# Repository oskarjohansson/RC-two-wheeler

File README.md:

# RC two wheeler
A 4 kW RC car with overkill BLDC motors and two VESCs and a 5 kW LiPo.  

## Hardware
- Flipsky VESC v4.12 x 2
- KEDA 63-64 190KV 2kW x 2
- Arduino Nano x2
- nRF24 x2
- 3S 60C 4000 mAh Turnigy Heavy duty LiPo
- Joystick 
- ~~2P2S N.E.S.E module x 2~~
- ~~Samsung 25E á 20A x 8~~
- ~~FrSky transmitter~~
- ~~RF Reciever~~

### PCB
- PWM/5V/GND in
- Nano
- nRF24 
- ON/OFF
- Battery
- Joystick  

## Software
- VESC Tool v0.95. 
- VSCode project for Nano.

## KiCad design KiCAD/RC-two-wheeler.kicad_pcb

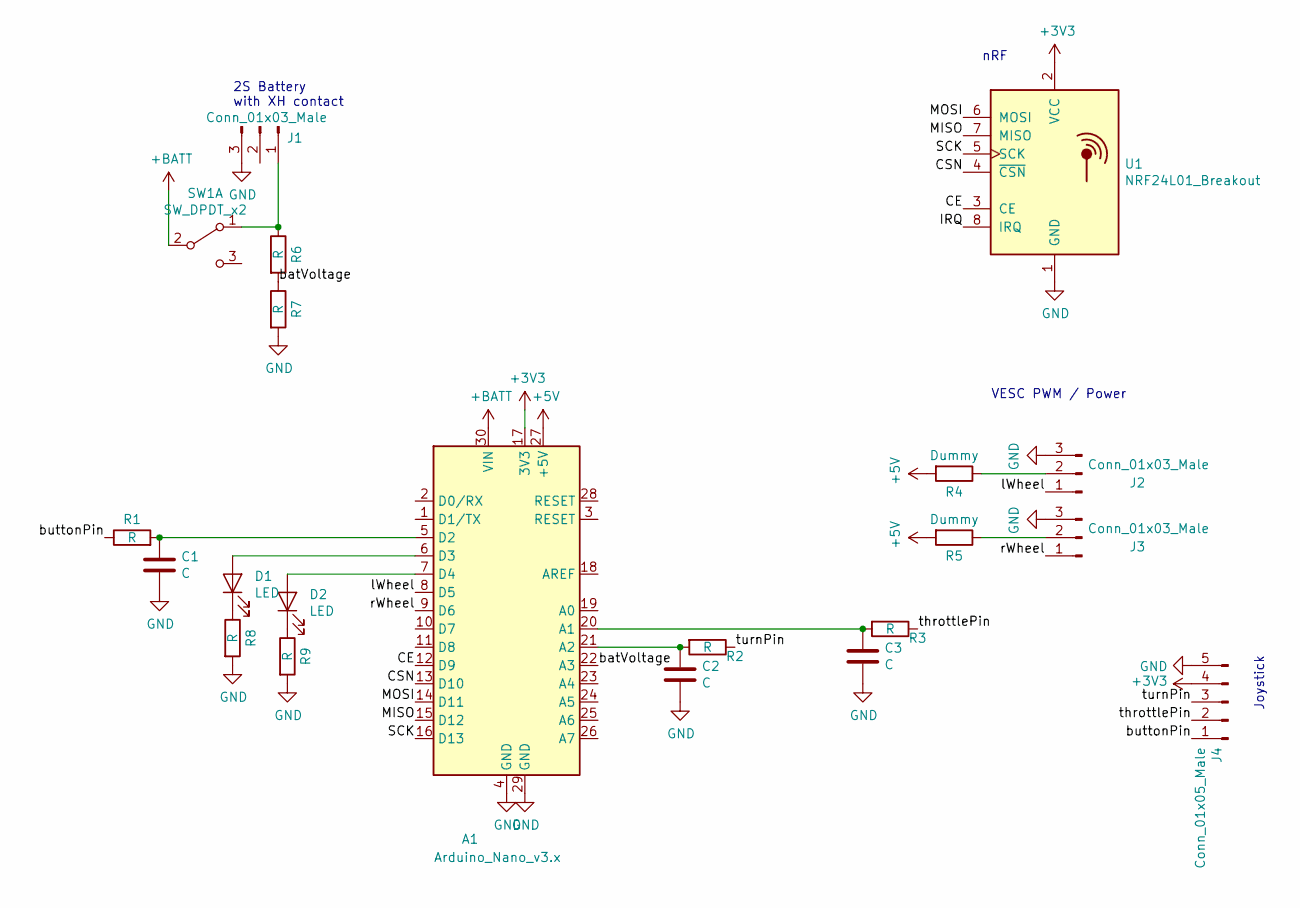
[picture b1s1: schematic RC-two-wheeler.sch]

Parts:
A1: Arduino_Nano_v3.x; Arduino_Nano
C1, C2, C3: C; C_0603_1608Metric_Pad1.05x0.95mm_HandSolder
D1, D2: LED; LED_0603_1608Metric_Pad1.05x0.95mm_HandSolder
J1, J2, J3: Conn_01x03_Male; JST_XH_B3B-XH-A_1x03_P2.50mm_Vertical
J4: Conn_01x05_Male; JST_XH_B5B-XH-A_1x05_P2.50mm_Vertical
R1, R2, R3, R6, R7, R8, R9: R; R_0603_1608Metric_Pad1.05x0.95mm_HandSolder
R4, R5: Dummy; R_0603_1608Metric_Pad1.05x0.95mm_HandSolder
SW1: SW_DPDT_x2; JS202011SCQN
U1: NRF24L01_Breakout; nRF24L01_Breakout

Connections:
+3V3: A1.17 (3V3), J4.4, U1.2 (VCC)
+5V: A1.27 (+5V), R4.2, R5.2
+BATT: A1.30 (VIN), SW1.2 (B)
/CE: A1.12 (D9), U1.3 (CE)
/CSN: A1.13 (D10), U1.4 (~CSN)
/IRQ: U1.8 (IRQ)
/MISO: A1.15 (D12), U1.7 (MISO)
/MOSI: A1.14 (D11), U1.6 (MOSI)
/SCK: A1.16 (D13), U1.5 (SCK)
/batVoltage: A1.22 (A3), R6.2, R7.1
/buttonPin: J4.1, R1.1
/lWheel: A1.8 (D5), J2.1
/rWheel: A1.9 (D6), J3.1
/throttlePin: J4.2, R3.1
/turnPin: J4.3, R2.1
GND: A1.4 (GND), A1.29 (GND), C1.2, C2.2, C3.2, J1.3, J2.3, J3.3, J4.5, R7.2, R8.2, R9.2, U1.1 (GND)
unnamed: A1.5 (D2), C1.1, R1.2
unnamed: A1.6 (D3), D1.2 (A)
unnamed: A1.7 (D4), D2.2 (A)
unnamed: A1.20 (A1), C3.1, R3.2
unnamed: A1.21 (A2), C2.1, R2.2
unnamed: D1.1 (K), R8.1
unnamed: D2.1 (K), R9.1
unnamed: J1.1, R6.1, SW1.1 (A)
unnamed: J2.2, R4.1
unnamed: J3.2, R5.1

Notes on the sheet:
VESC PWM / Power
Joystick
2S Battery with XH contact
nRF

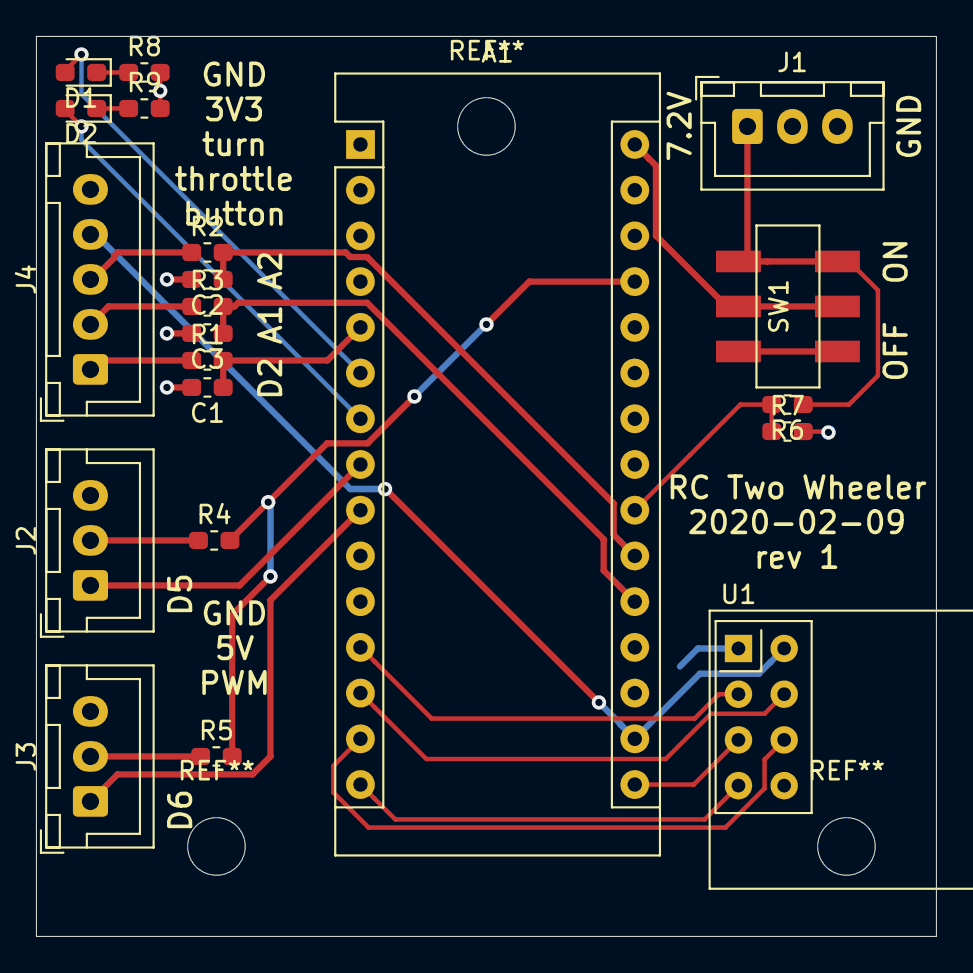
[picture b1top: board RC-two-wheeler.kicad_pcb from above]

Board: 2 copper layers, 50.0 x 50.0 mm, 21 parts (0 on the bottom side), 25 nets.

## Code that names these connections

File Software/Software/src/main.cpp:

/**
 * @file main.cpp
 * @author Oskar Johansson (oskar@irisnet.se)
 * @brief This project is to work with 2 MCU and 2 nRF24 to communicate throttle and turn. Based on 
 *        https://github.com/caselabbet/case-rc-car by Isak Åslund. 
 * @version 0.1
 * @date 2020-01-29 
 */
#include <Arduino.h>
#include <SoftwareSerial.h>
#include <Servo.h>
#include <RF24.h>


// Choose which to compile for 
#define reciever
//#define transmitter 
#define DEBUG

/**
 * To reuse same code for reciever and trasmitter 
 */


/**
 * Pin definition, same for reciever as transmitter
 */
#define lWheelPin 5
#define rWheelPin 6
#define throttlePin A1
#define turnPin A2
#define CE 9 
#define CSN 10

RF24 radio(CE,CSN); 
const byte address[6] = "00010";    // Adress for communicating
unsigned long lastData = 0;         // Used for knowing if data has been received recently
unsigned long lasttime = millis();  // To track of how long time since last transmitt / recieve 
int throttleComp = 0; 
int turnComp = 0;
bool setupOk = false; 
/**
 * A struct to store the recieved 
 * throttle and turn  
 */
typedef struct{
    int throttle;
    int turn;
}message_t;                         // Struct for making sending/receiving easy
message_t msg;
message_t analog; 
/**
 * Create the wheels 
 */
Servo lWheel, rWheel;

#define NOSPEED 90            // In servo degree
#define DEFAULTSPEED 20       // In servo degree
#define MAXSPEED 45           // In servo degree
#define MAXTURN 20            // In servo degree 
#define MAX_TIMEOUT 500       // in ms


/**
 * @brief Reciever:   Write the throttle and turn to the 
 *                    left and right wheel. Also checks
 *                    if the input values are to high/low. 
 *                    A turn is simply throttle+-turn on
 *                    this two-wheeler. 
 * 
 * @param throttle  - The throttle 0 - 180 
 * @param turn      - The turn 0 - 180
 */
void writeToWheels(int throttle, int turn) {
  int lSpeed = NOSPEED; int rSpeed = NOSPEED; 
  // 0 is max, 90 is still, 180 max reverse
  if(throttle < MAXSPEED)
    throttle = MAXSPEED; 
  else if (throttle > (MAXSPEED+90))
    throttle = MAXSPEED+90; 
  
  // Check so the turn speed isn't to fast 
  if(turn < MAXTURN)
    turn = MAXTURN;
  else if (turn > MAXTURN+90)
    turn = MAXTURN + 90; 
  // 
  turn -= 90; 
  // To check if it wasn't to long ago the input was recieved 
  if((millis() - lasttime)< MAX_TIMEOUT) {
    lSpeed = throttle+turn/2; 
    rSpeed = throttle-turn/2; 
  }
  
  // Write to output
  lWheel.write(lSpeed);
  rWheel.write(rSpeed);
  
  #ifdef DEBUG
      Serial.print("Input throttle: "); Serial.print(throttle); Serial.print("\t input turn: "); Serial.println(turn);
      Serial.print("Left output: "); Serial.print(lSpeed); Serial.print("\t \t Right output: "); Serial.println(rSpeed);
  #endif 
}

/**
 * @brief Transmitter:  Convert analog in signal to a throttle
 *                      level and write to nRF. 
 * 
 * @return true   - If successful transmitt
 * @return false  - If fail in writing to nRF
 */
bool writeToRadio() {
    // Convert to a servo signal (0 - 180 degrees) 90 is still, 0 max, 180 max
    msg.throttle = analog.throttle * 180.0 / 1024.0; 
    msg.turn = analog.turn * 180.0 / 1024.0; 
    bool succ = radio.write(&msg,sizeof(msg));
    #ifdef DEBUG
      Serial.print("Sent throttle: "); Serial.print(msg.throttle); Serial.print("\t sent turn: "); Serial.print(msg.turn); Serial.print(" successful transmitt: "); Serial.println(succ);
    #endif 
    return succ; 
}

/**
 * @brief Transmitter:  Write to nRF the throttle and turn. 
 *        Reciever:     Write the input from nRF to servo.  
 */
void writeOutput() {
  #ifdef transmitter
    writeToRadio(); 
  #else 
      writeToWheels(msg.throttle, msg.turn); 
  #endif
}


/**
 * @brief Transmitter:  Reads the analog value from joystick.
 *        Reciever:     See if new data available on nRF and 
 *                      save it to msg.  
 */
void readInput() {
  #ifdef transmitter 
    // Read the analog input with a simple LP filter
    analog.throttle = (analog.throttle + (analogRead(throttlePin)+throttleComp))/2;
    analog.turn = (analog.turn + (analogRead(turnPin)+turnComp))/2;
    #ifdef DEBUG
      Serial.print("Read throttle: "); Serial.print(analog.throttle); Serial.print("\t read turn: "); Serial.println(analog.turn);
    #endif 
  #else
    #ifdef DEBUG
      Serial.print("Radio available: "); Serial.println(radio.available());
    #endif 
    if(radio.available()) {
      radio.read(&msg, sizeof(msg)); 
      lasttime = millis(); 
      #ifdef DEBUG
        Serial.println("Recieved new input!");
      #endif
    } 
  #endif
}


/**
 * @brief Setup module as transmitter and sets analog input from joystick. 
 *        Also compensate for joystick value. Sets current value as new 0. 
 * 
 * @return true  - If able to connect setup nRF module
 * @return false - If unable to connect and setup nRf module
 */
bool setupTransmitter() {
  // Analog read for throttle and turn value
  pinMode(throttlePin, INPUT);
  pinMode(turnPin, INPUT);
  
  // To compensate for bad joystick
  // sets the current value as "middle" value. 
  throttleComp = 512 - analogRead(throttlePin);
  turnComp = 512 - analogRead(turnPin);
  
  // Start the nRF 
  if(radio.begin()) {
    #ifdef DEBUG
      Serial.println("Radio has begun!");
    #endif
  } 
  radio.openWritingPipe(address);
  radio.setPALevel(RF24_PA_MAX); 
  radio.setRetries(3,5); // delay, count
  radio.setDataRate(RF24_250KBPS);
  //radio.stopListening();
  
  // Return 1 if found nRf connected, 0 else
  return radio.isChipConnected();
}

/**
 * @brief Setup nRF module and the servo pins. 
 * 
 * @return true  - If able to connect setup nRF module
 * @return false - If unable to connect and setup nRf module
 */
bool setupReciever() {
    // Attach PWM pins for wheel signal
    lWheel.attach(lWheelPin);
    rWheel.attach(rWheelPin);
    // Write 90 deg (zero in speed)
    lWheel.write(NOSPEED);
    rWheel.write(NOSPEED);
    msg.throttle = NOSPEED;
    msg.turn = NOSPEED; 

    // Start the nRf 
    radio.begin();
    radio.openReadingPipe(1, address);
    //radio.setPALevel(RF24_PA_MAX);
    radio.setDataRate(RF24_250KBPS);
    radio.startListening();

    // Return 1 if found nRf connected, 0 else
    return radio.isChipConnected();
}


void setup() {
  #ifdef DEBUG
  Serial.begin(9600);
  #endif 


  #ifdef transmitter 
    setupOk = setupTransmitter(); 
  #else 
    setupOk = setupReciever();
  #endif 
}

void loop() {
  readInput(); 
  writeOutput();
}

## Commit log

2019-05-20 Create part, not finished
    Not finished
2019-05-20 Just update
2019-05-20 First draft
2019-05-23 Updated wheel and made it two seperated
2019-07-09 Created firmware setup in PIO
2019-07-09 Added servo lib
2019-07-09 Workning firmware
    The firmware is now working with BT-device and Car bluetooth app on android
2019-07-09 Updated design
2020-01-29 Added wheels
2020-01-29 Create gitignore and ignore OldVersions folder
2020-01-29 Added RF24 lib
    From https://github.com/nRF24/RF24
2020-01-29 Complete code for first version
    Same code for reciever and transmitter. Just a define in the beginning to compile for one och another.
2020-01-30 Comment code a little
2020-01-30 Added debug and comment code
    Quite huge update on the code. The nRF is implemented and "working" now. Data can be seen sent and recieved by two Nano.
2020-01-31 Changed to latest hardware components
    Now using two Arduino Nano with nRF24 to communicate instead of a real transmitter.
2020-01-31 Added max transmitt level
2020-02-03 Created a KiCAD project
2020-02-05 Routed the board, must double check LiPo con!
2020-02-09 Added 2 led and made DRC
2020-02-09 Updated rev date to 20200209
2020-02-09 Generate gerber files and order
